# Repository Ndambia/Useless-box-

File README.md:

# Useless-box-
Single and Five switch uselessbox

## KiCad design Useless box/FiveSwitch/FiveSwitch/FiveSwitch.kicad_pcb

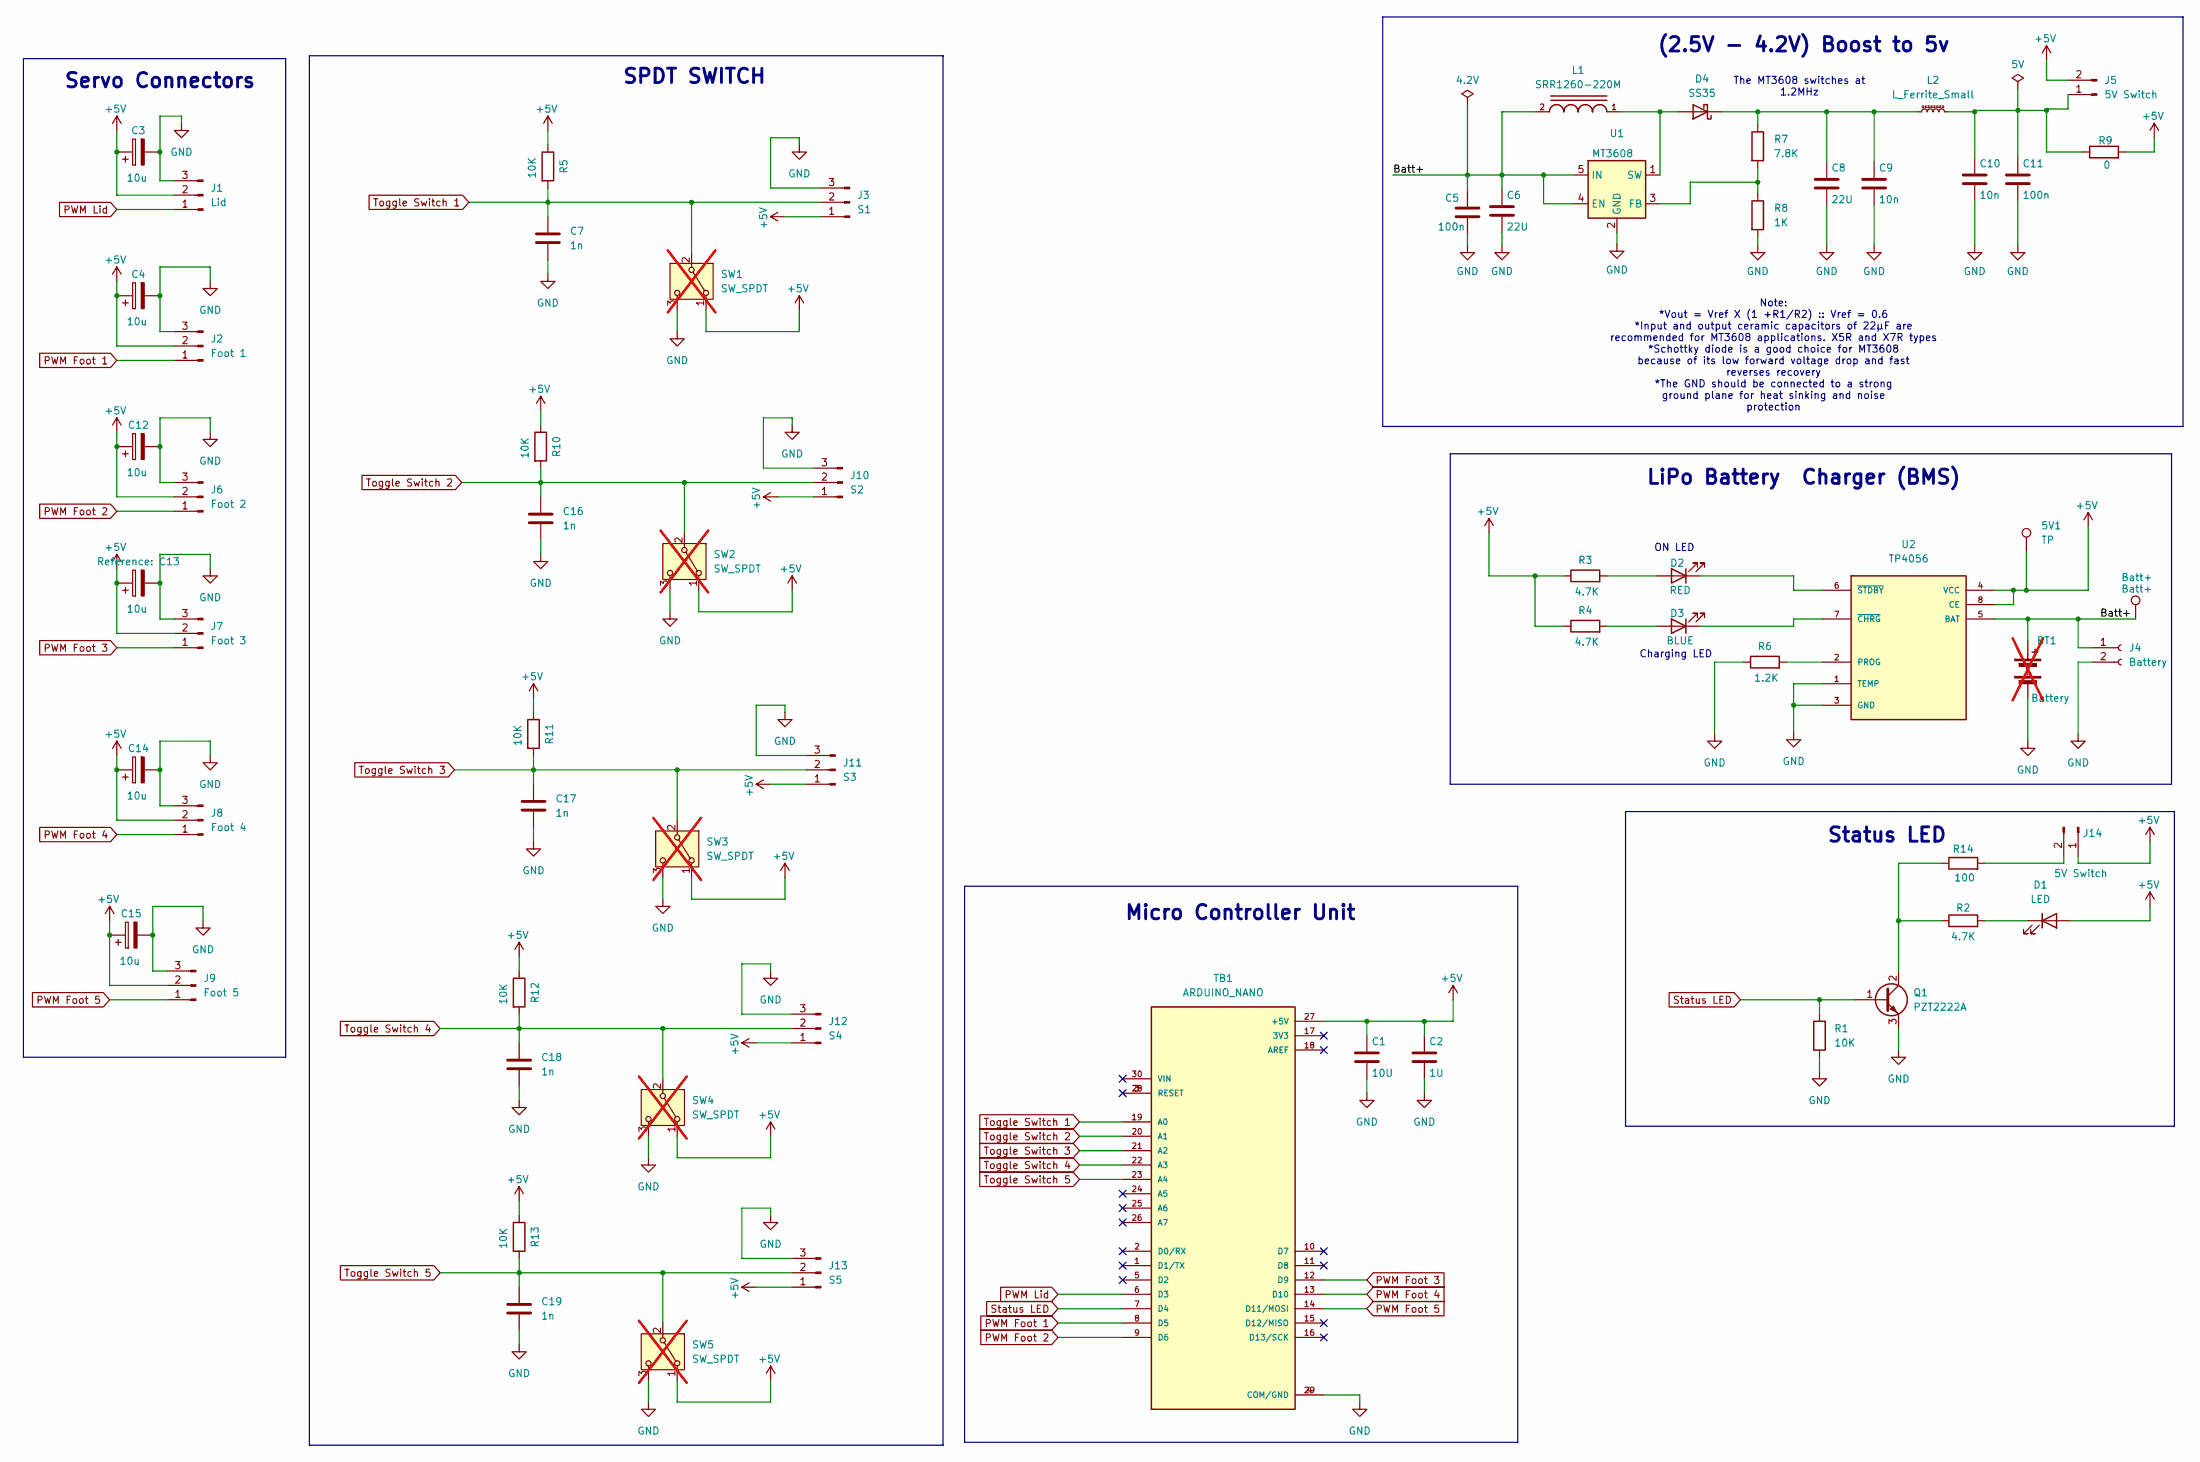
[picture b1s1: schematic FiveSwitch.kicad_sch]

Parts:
5V1: TP; TestPoint_Pad_D1.5mm
BT1: Battery; not fitted
Batt+: Batt+; TestPoint_Pad_D1.5mm
C1: 10U; C_0603_1608Metric
C2: 1U; C_0603_1608Metric
C3, C4, C12, C13, C14, C15: 10u; C_0603_1608Metric
C5: 100n; C_0603_1608Metric
C6, C8: 22U; C_0603_1608Metric
C7, C16, C17, C18, C19: 1n; C_0603_1608Metric
C9: 10n; C_0603_1608Metric
C10: 10n; C_0402_1005Metric
C11: 100n; C_0402_1005Metric
D1: LED; LED_0603_1608Metric
D2: RED; LED_0402_1005Metric
D3: BLUE; LED_0402_1005Metric
D4: SS35; D_SMA
J1: Lid; PinHeader_1x03_P2.54mm_Vertical
J2: Foot 1; PinHeader_1x03_P2.54mm_Vertical
J3: S1; PinHeader_1x03_P2.54mm_Vertical
J4: Battery; JST_EH_B2B-EH-A_1x02_P2.50mm_Vertical
J5, J14: 5V Switch; PinHeader_1x02_P2.54mm_Vertical
J6: Foot 2; PinHeader_1x03_P2.54mm_Vertical
J7: Foot 3; PinHeader_1x03_P2.54mm_Vertical
J8: Foot 4; PinHeader_1x03_P2.54mm_Vertical
J9: Foot 5; PinHeader_1x03_P2.54mm_Vertical
J10: S2; PinHeader_1x03_P2.54mm_Vertical
J11: S3; PinHeader_1x03_P2.54mm_Vertical
J12: S4; PinHeader_1x03_P2.54mm_Vertical
J13: S5; PinHeader_1x03_P2.54mm_Vertical
L1: SRR1260-220M; INDP125125X600N
L2: L_Ferrite_Small; L_0603_1608Metric
Q1: PZT2222A; SOT-223-3_TabPin2
R1: 10K; R_0402_1005Metric
R2: 4.7K; R_0402_1005Metric
R3, R4: 4.7K; R_0603_1608Metric
R5, R10, R11, R12, R13: 10K; R_0603_1608Metric
R6: 1.2K; R_0603_1608Metric
R7: 7.8K; R_0603_1608Metric
R8: 1K; R_0603_1608Metric
R9: 0; R_0402_1005Metric
R14: 100; R_0402_1005Metric
SW1, SW2, SW3, SW4, SW5: SW_SPDT; not fitted
TB1: ARDUINO_NANO; MODULE_ABX00028
U1: MT3608; SOT-23-6
U2: TP4056; SOP127P600X175-9N

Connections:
+5V: 5V1.1, C1.1, C2.1, C3.1, C4.1, C12.1, C13.1, C14.1, C15.1, D1.2 (A), J1.2, J2.2, J3.1, J5.2, J6.2, J7.2, J8.2, J9.2, J10.1, J11.1, J12.1, J13.1, J14.1, R3.1, R4.1, R5.1, R9.2, R10.1, R11.1, R12.1, R13.1, SW1.1 (A), SW2.1 (A), SW3.1 (A), SW4.1 (A), SW5.1 (A), TB1.27 (+5V), U2.4 (VCC), U2.8 (CE)
/Batt+: BT1.1 (+), Batt+.1, C5.1, C6.1, J4.1, L1.2, U1.4 (EN), U1.5 (IN), U2.5 (BAT)
GND: BT1.2 (-), C1.2, C2.2, C3.2, C4.2, C5.2, C6.2, C7.2, C8.2, C9.2, C10.2, C11.2, C12.2, C13.2, C14.2, C15.2, C16.2, C17.2, C18.2, C19.2, J1.3, J2.3, J3.3, J4.2, J6.3, J7.3, J8.3, J9.3, J10.3, J11.3, J12.3, J13.3, Q1.3 (E), R1.1, R6.1, R8.2, SW1.3 (C), SW2.3 (C), SW3.3 (C), SW4.3 (C), SW5.3 (C), TB1.4 (COM/GND), TB1.29 (COM/GND), U1.2 (GND), U2.1 (TEMP), U2.3 (GND)
unnamed: D1.1 (K), R2.2
unnamed: D2.2 (A), R3.2
unnamed: D2.1 (K), U2.6 (~STDBY)
unnamed: D3.2 (A), R4.2
unnamed: D3.1 (K), U2.7 (~CHRG)
unnamed: D4.2 (A), L1.1, U1.1 (SW)
unnamed: C8.1, C9.1, D4.1 (K), L2.1, R7.1
unnamed: C10.1, C11.1, J5.1, L2.2, R9.1
unnamed: J14.2, R14.2
unnamed: Q1.2 (C), R2.1, R14.1
unnamed: R7.2, R8.1, U1.3 (FB)
unnamed: R6.2, U2.2 (PROG)
PWM Foot 1: J2.1, TB1.8 (D5)
PWM Foot 2: J6.1, TB1.9 (D6)
PWM Foot 3: J7.1, TB1.12 (D9)
PWM Foot 4: J8.1, TB1.13 (D10)
PWM Foot 5: J9.1, TB1.14 (D11/MOSI)
PWM Lid: J1.1, TB1.6 (D3)
Status LED: Q1.1 (B), R1.2, TB1.7 (D4)
Toggle Switch 1: C7.1, J3.2, R5.2, SW1.2 (B), TB1.19 (A0)
Toggle Switch 2: C16.1, J10.2, R10.2, SW2.2 (B), TB1.20 (A1)
Toggle Switch 3: C17.1, J11.2, R11.2, SW3.2 (B), TB1.21 (A2)
Toggle Switch 4: C18.1, J12.2, R12.2, SW4.2 (B), TB1.22 (A3)
Toggle Switch 5: C19.1, J13.2, R13.2, SW5.2 (B), TB1.23 (A4)

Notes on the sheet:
ON LED
Charging LED
Servo Connectors
LiPo Battery Charger (BMS)
The MT3608 switches at 1.2MHz
Status LED
(2.5V - 4.2V) Boost to 5v
Note: *Vout = Vref X (1 +R1/R2) :: Vref = 0.6 *Input and output ceramic capacitors of 22μF are recommended for MT3608 applications. X5R and X7R types *Schottky diode is a good choice for MT3608 because of its low forward voltage drop and fast reverses recovery *The GND should be connected to a stro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
Micro Controller Unit
SPDT SWITCH

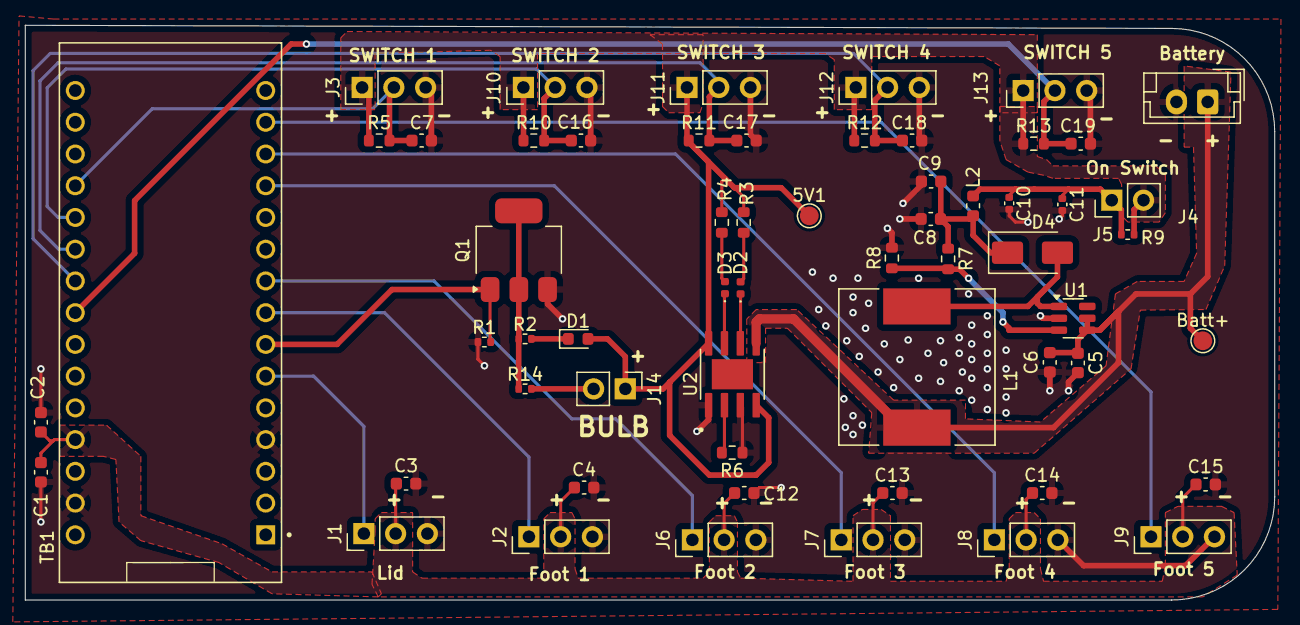
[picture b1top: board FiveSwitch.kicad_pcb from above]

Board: 2 copper layers, 100.0 x 46.0 mm, 59 parts (0 on the bottom side), 27 nets.

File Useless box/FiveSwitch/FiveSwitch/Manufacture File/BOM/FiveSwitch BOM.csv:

Reference,Value,Footprint,Qty,Manufacturer Part No,Supplier
C1,10U,Capacitor_SMD:C_0603_1608Metric,1,CL10A106KP8NNNC,LCSC
C2,1U,Capacitor_SMD:C_0603_1608Metric,1,CL10A105KB8NNNC,LCSC
"C3,C4,C12,C13,C14,C15",10u,Capacitor_SMD:C_0603_1608Metric,6,CL10A106KP8NNNC,LCSC
C5,100n,Capacitor_SMD:C_0603_1608Metric,1,CC0603KRX7R6BB104,LCSC
"C6,C8",22U,Capacitor_SMD:C_0603_1608Metric,2,CL10A226MP8NUNE,LCSC
"C7,C16,C17,C18,C19",1n,Capacitor_SMD:C_0603_1608Metric,5,CC0603KRX7R6BB102,LCSC
C9,10n,Capacitor_SMD:C_0603_1608Metric,1,CC0603KRX7R6BB103,LCSC
C10,CC0402KRX7R9BB103,Capacitor_SMD:C_0402_1005Metric,1,CC0402KRX7R9BB103,LCSC
C11,CL05B104KO5NNNC,Capacitor_SMD:C_0402_1005Metric,1,CL05B104KO5NNNC,LCSC
D1,LED,LED_SMD:LED_0603_1608Metric,1,XL-1608SURC-06,LCSC
D2,SZYY0402R,LED_SMD:LED_0402_1005Metric,1,SZYY0402R,LCSC
D3,BLUE,LED_SMD:LED_0402_1005Metric,1,XL-1005UBC,LCSC
D4,SS35,Diode_SMD:D_SMA,1,SS35,LCSC
J1,PZ254V-11-03P,Connector_PinHeader_2.54mm:PinHeader_1x03_P2.54mm_Vertical,1,PZ254V-11-03P,LCSC
J2,PZ254V-11-03P,Connector_PinHeader_2.54mm:PinHeader_1x03_P2.54mm_Vertical,1,PZ254V-11-03P,LCSC
J3,PZ254V-11-03P,Connector_PinHeader_2.54mm:PinHeader_1x03_P2.54mm_Vertical,1,PZ254V-11-03P,LCSC
J4,B2B-EH-A(LF)(SN),Connector_JST:JST_EH_B2B-EH-A_1x02_P2.50mm_Vertical,1,B2B-EH-A(LF)(SN),LCSC
"J5,J14",5V Switch,Connector_PinHeader_2.54mm:PinHeader_1x02_P2.54mm_Vertical,2,PZ254V-11-02P,LCSC
J6,PZ254V-11-03P,Connector_PinHeader_2.54mm:PinHeader_1x03_P2.54mm_Vertical,1,PZ254V-11-03P,LCSC
J7,PZ254V-11-03P,Connector_PinHeader_2.54mm:PinHeader_1x03_P2.54mm_Vertical,1,PZ254V-11-03P,LCSC
J8,PZ254V-11-03P,Connector_PinHeader_2.54mm:PinHeader_1x03_P2.54mm_Vertical,1,PZ254V-11-03P,LCSC
J9,PZ254V-11-03P,Connector_PinHeader_2.54mm:PinHeader_1x03_P2.54mm_Vertical,1,PZ254V-11-03P,LCSC
J10,PZ254V-11-03P,Connector_PinHeader_2.54mm:PinHeader_1x03_P2.54mm_Vertical,1,PZ254V-11-03P,LCSC
J11,PZ254V-11-03P,Connector_PinHeader_2.54mm:PinHeader_1x03_P2.54mm_Vertical,1,PZ254V-11-03P,LCSC
J12,PZ254V-11-03P,Connector_PinHeader_2.54mm:PinHeader_1x03_P2.54mm_Vertical,1,PZ254V-11-03P,LCSC
J13,PZ254V-11-03P,Connector_PinHeader_2.54mm:PinHeader_1x03_P2.54mm_Vertical,1,PZ254V-11-03P,LCSC
L1,SRR1260-220M,Power Inductor:INDP125125X600N,1,SRR1260-220M,LCSC
L2,L_Ferrite_Small,Inductor_SMD:L_0603_1608Metric,1,BLM18PG121SN1D,LCSC
Q1,PZT2222A,Package_TO_SOT_SMD:SOT-223-3_TabPin2,1,PZT2222A,LCSC
R1,RC0402FR-0710KL,Resistor_SMD:R_0402_1005Metric,1,RC0402FR-0710KL,LCSC
R2,RC0402FR-074K7L,Resistor_SMD:R_0402_1005Metric,1,RC0402FR-074K7L,LCSC
"R3,R4",4.7K,Resistor_SMD:R_0603_1608Metric,2,0603WAF4701T5E,LCSC
"R5,R10,R11,R12,R13",10K,Resistor_SMD:R_0603_1608Metric,5,0603WAF1002T5E,LCSC
R6,1.2K,Resistor_SMD:R_0603_1608Metric,1,0603WAJ0122T5E,LCSC
R7,7.8K,Resistor_SMD:R_0603_1608Metric,1,AR03BTCX7801N,LCSC
R8,1K,Resistor_SMD:R_0603_1608Metric,1,0603WAF1001T5E,LCSC
R14,RC0402JR-07100RL,Resistor_SMD:R_0402_1005Metric,1,RC0402JR-07100RL,LCSC
U1,MT3608,Package_TO_SOT_SMD:SOT-23-6,1,MT3608,LCSC
U2,TP4056,TP4056:SOP127P600X175-9N,1,TP4056,LCSC

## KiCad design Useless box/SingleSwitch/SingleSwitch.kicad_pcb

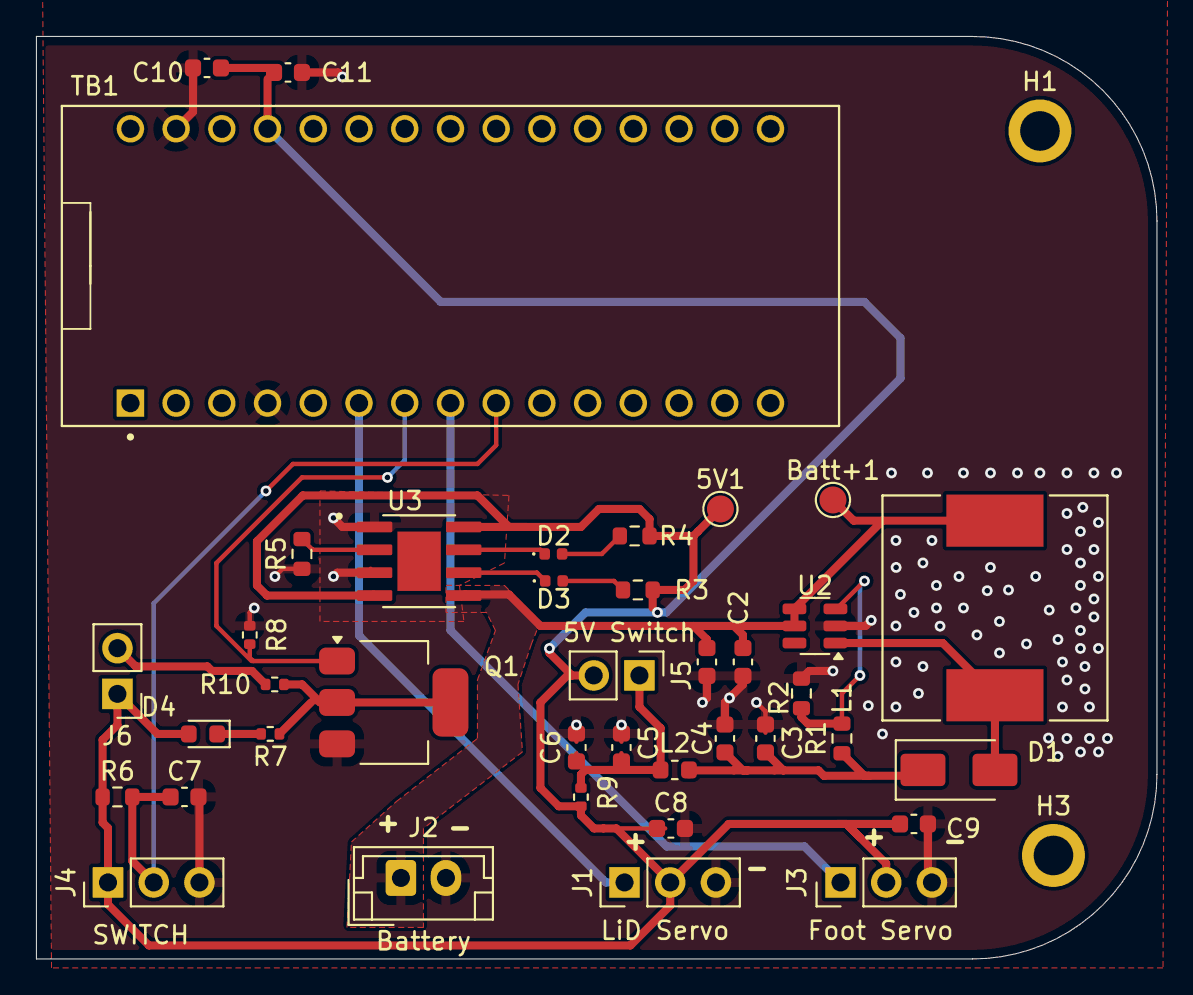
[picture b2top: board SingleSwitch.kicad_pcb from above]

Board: 2 copper layers, 62.2 x 51.2 mm, 41 parts (0 on the bottom side), 19 nets.

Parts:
5V1: TP; TestPoint_Pad_D1.5mm
Batt+1: Batt+; TestPoint_Pad_D1.5mm
C1, C6: 100n; C_0603_1608Metric
C2, C3: 22U; C_0603_1608Metric
C4, C5: 10n; C_0603_1608Metric
C7: 1n; C_0603_1608Metric
C8, C9: 10u; C_0603_1608Metric
C10, C11: 10U; C_0603_1608Metric
D1: SS35; D_SMA
D2: BLUE; LED_0402_1005Metric
D3: RED; LED_0402_1005Metric
D4: LED; LED_0603_1608Metric
H1, H3: MountingHole; MountingHole_2.2mm_M2_ISO7380_Pad
J1, J3, J4: Conn_01x03_Pin; PinHeader_1x03_P2.54mm_Vertical
J2: Battery; JST_EH_B2B-EH-A_1x02_P2.50mm_Vertical
J5: 5V Switch; PinHeader_1x02_P2.54mm_Vertical
J6: Bulb terminal; PinHeader_1x02_P2.54mm_Vertical
L1: SRR1260-220M; INDP125125X600N
L2: L_Ferrite_Small; L_0603_1608Metric
Q1: PZT2222A; SOT-223-3_TabPin2
R1: 7.8K; R_0603_1608Metric
R2: 1K; R_0603_1608Metric
R3, R4: 4.7K; R_0603_1608Metric
R5: 1.2K; R_0603_1608Metric
R6: 10K; R_0603_1608Metric
R7: 1K; R_0402_1005Metric
R8: 10K; R_0402_1005Metric
R9: 0; R_0402_1005Metric
R10: 100; R_0402_1005Metric
TB1: ARDUINO_NANO; MODULE_ABX00028
U2: MT3608; SOT-23-6
U3: TP4056; SOP127P600X175-9N

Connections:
+5V: 5V1.1, C8.1, C9.1, C10.1, C11.1, D4.2 (A), J1.2, J3.2, J4.1, J5.2, J6.1, R3.1, R4.1, R6.1, R9.2, TB1.27 (+5V), U3.4 (VCC), U3.8 (CE)
/Batt+: Batt+1.1, C1.1, C2.1, J2.1, L1.2, U2.4 (EN), U2.5 (IN), U3.5 (BAT)
GND: C1.2, C2.2, C3.2, C4.2, C5.2, C6.2, C7.2, C8.2, C9.2, C10.2, C11.2, J1.3, J2.2, J3.3, J4.3, Q1.3 (E), R2.2, R5.1, R8.1, TB1.4 (COM/GND), TB1.29 (COM/GND), U2.2 (GND), U3.1 (TEMP), U3.3 (GND)
unnamed: D1.2 (A), L1.1, U2.1 (SW)
unnamed: C3.1, C4.1, D1.1 (K), L2.1, R1.1
unnamed: D2.2 (A), R4.2
unnamed: D2.1 (K), U3.7 (~CHRG)
unnamed: D3.2 (A), R3.2
unnamed: D3.1 (K), U3.6 (~STDBY)
unnamed: D4.1 (K), R7.2
unnamed: C5.1, C6.1, J5.1, L2.2, R9.1
unnamed: J6.2, R10.2
unnamed: Q1.2 (C), R7.1, R10.1
unnamed: R1.2, R2.1, U2.3 (FB)
unnamed: R5.2, U3.2 (PROG)
PWM Foot: J3.1, TB1.8 (D5)
PWM Lid: J1.1, TB1.6 (D3)
Status LED: Q1.1 (B), R8.2, TB1.7 (D4)
Toggle Switch: C7.1, J4.2, R6.2, TB1.9 (D6)

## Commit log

2024-12-29 Useless project include kicad files, all manufacturing files for a single switch and five switch uselessbox
